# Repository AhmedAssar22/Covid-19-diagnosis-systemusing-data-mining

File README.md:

# Covid-19-diagnosis-systemusing-data-mining
Covid-19 diagnosis system using data mining to identify people who are sick with Covid-19 by using other data for sick or healthy people through data such as temperature, oxygen percentage, and training the system again and again to increase its efficiency. I applied a computer and sent it to the deep learning system using Java and compared it with the information stored in the system. I designed the sensor system and programmed it using the C language, and I contributed to programming part of the deep learning system

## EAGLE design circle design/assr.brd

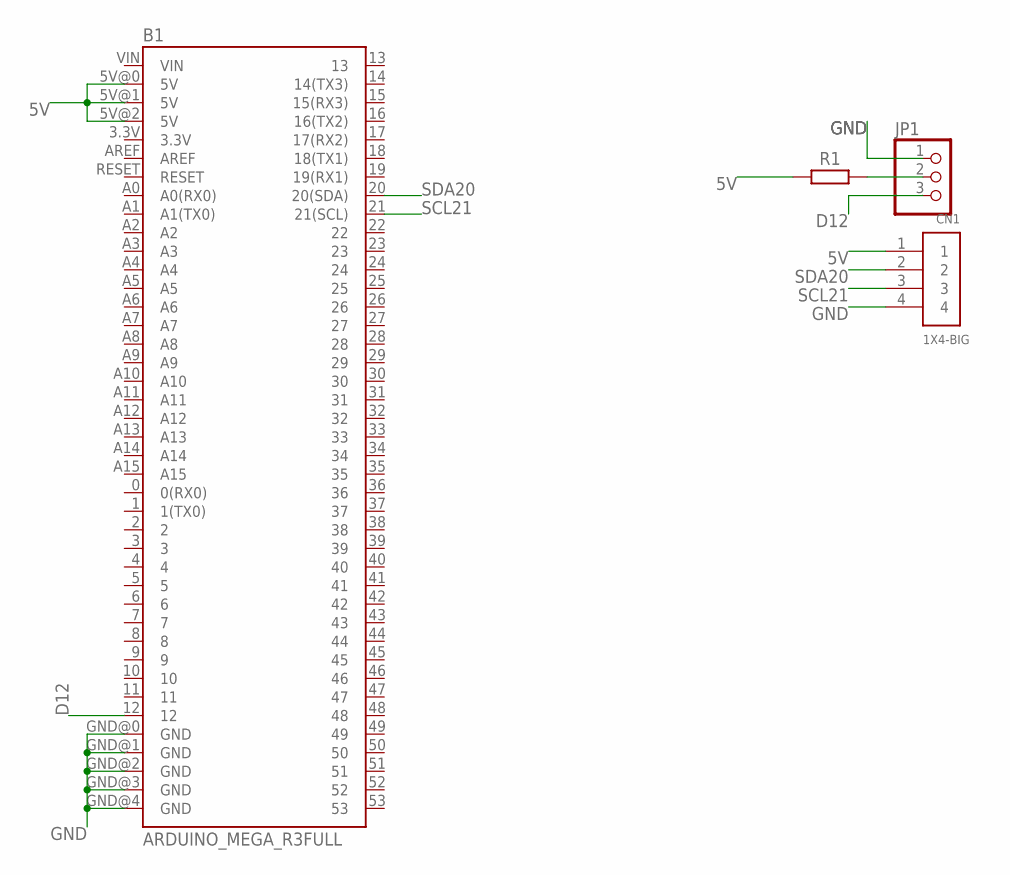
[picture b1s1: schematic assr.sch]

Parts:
B1: ARDUINO_MEGA_R3FULL; ARDUINO_MEGA
CN1: 1X4-BIG; 1X04-BIG
JP1: PINHD-1X3CB; 1X03-CLEANBIG
R1: R_AXIAL-11.7MM-PITCH; RESAD1176W63L850D250B

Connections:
5V: B1.5V@0 (5V), B1.5V@1 (5V), B1.5V@2 (5V), CN1.1, R1.1
D12: B1.12, JP1.3
GND: B1.GND@0 (GND), B1.GND@1 (GND), B1.GND@2 (GND), B1.GND@3 (GND), B1.GND@4 (GND), CN1.4, JP1.1
unnamed: JP1.2, R1.2
SCL21: B1.21 (21(SCL)), CN1.3
SDA20: B1.20 (20(SDA)), CN1.2

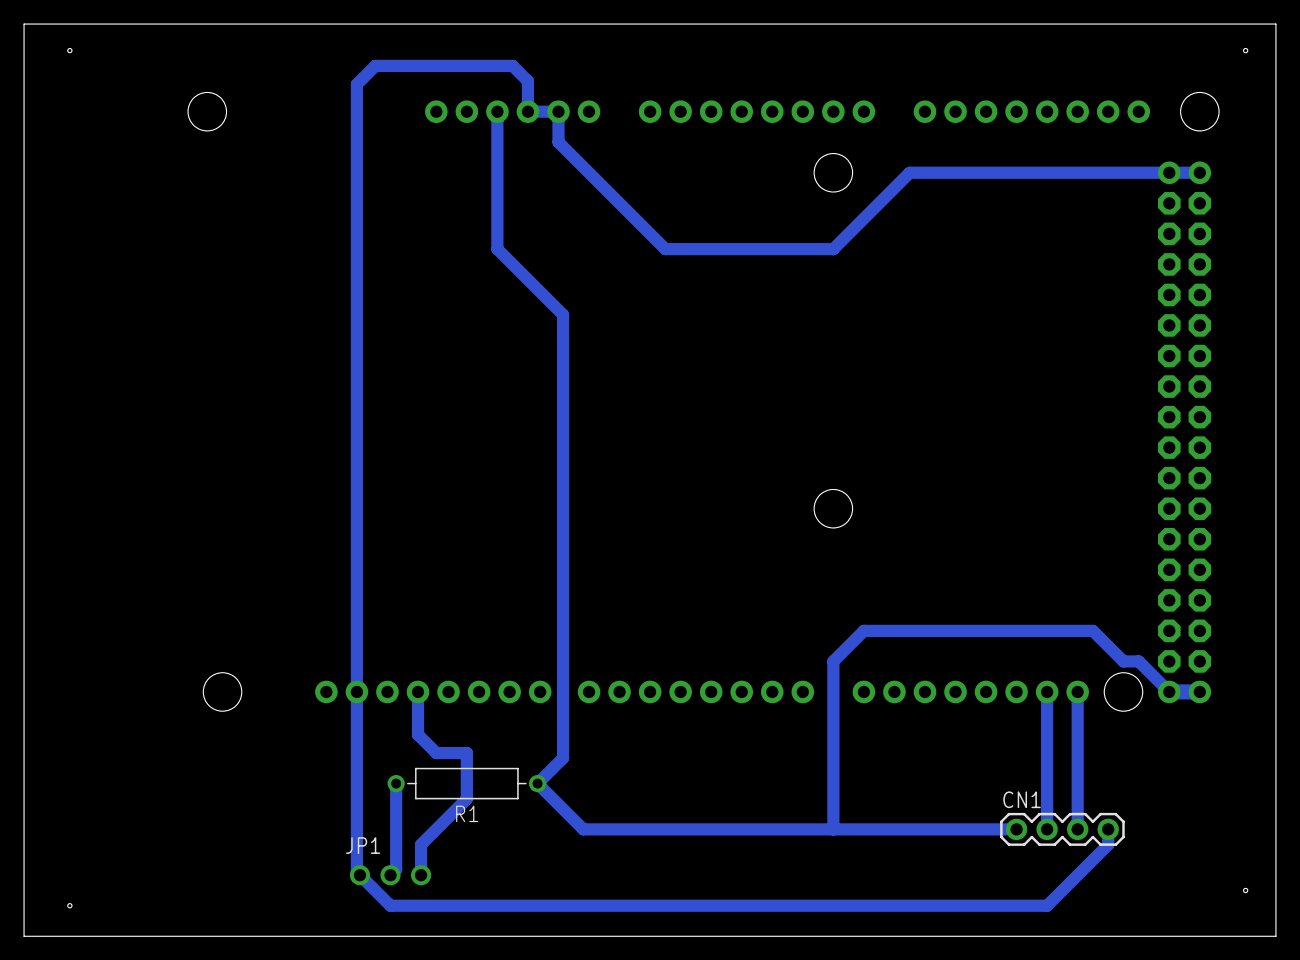
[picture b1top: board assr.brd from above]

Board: 2 copper layers, 104.1 x 75.9 mm, 4 parts (1 on the bottom side), 6 nets.

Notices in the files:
parts and their libraries:
SparkFun-Boards: Licensing: Creative Commons ShareAlike 4.0 International - https://creativecommons.org/licenses/by-sa/4.0
